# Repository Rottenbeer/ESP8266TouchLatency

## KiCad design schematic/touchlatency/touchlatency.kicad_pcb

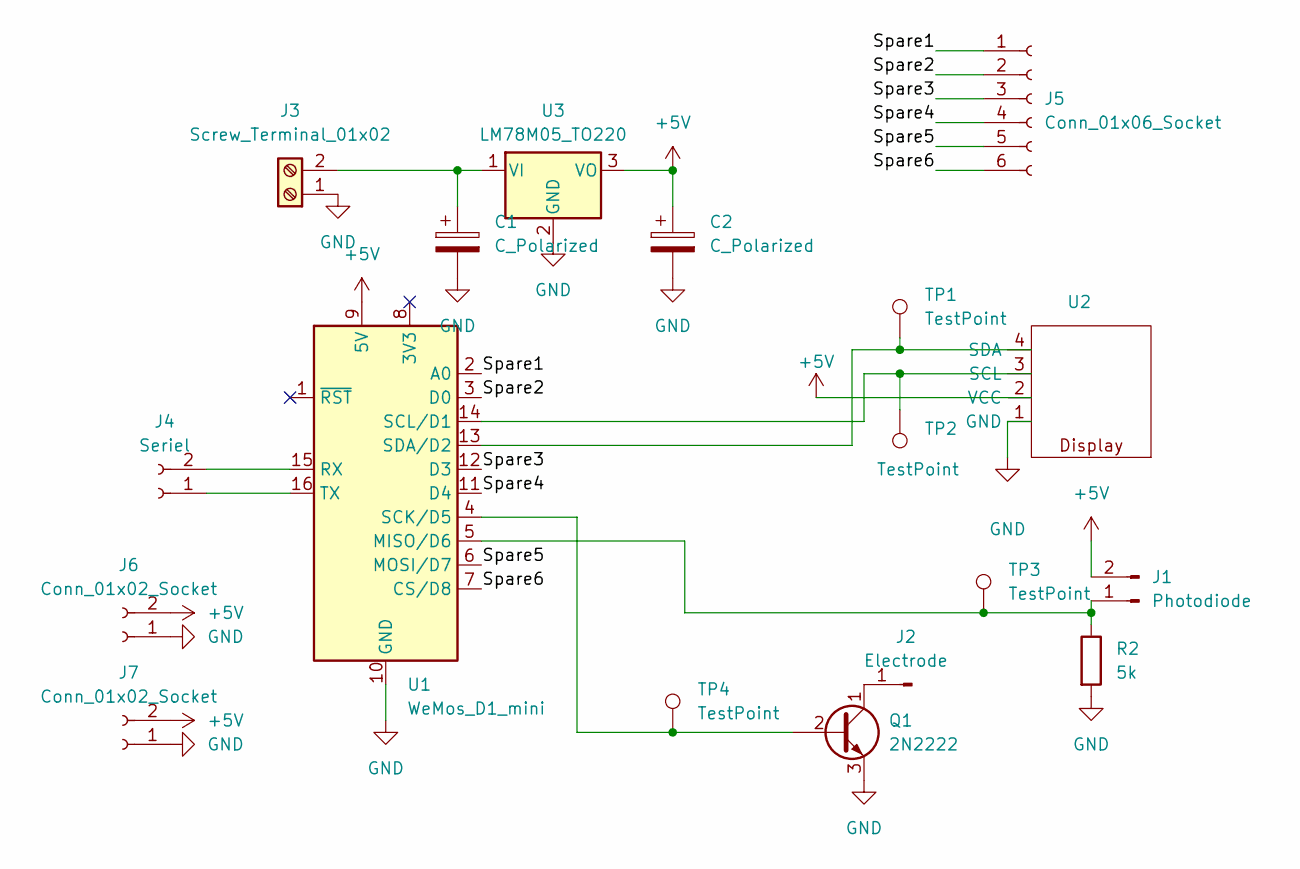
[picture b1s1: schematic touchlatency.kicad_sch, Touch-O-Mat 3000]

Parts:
C1, C2: C_Polarized; CP_Radial_D6.3mm_P2.50mm
J1: Photodiode; PinHeader_1x02_P2.54mm_Vertical
J2: Electrode; PinHeader_1x01_P2.54mm_Vertical
J3: Screw_Terminal_01x02; TerminalBlock_Altech_AK300-2_P5.00mm
J4: Seriel; PinHeader_1x02_P2.54mm_Vertical
J5: Conn_01x06_Socket; PinHeader_1x06_P2.54mm_Vertical
J6, J7: Conn_01x02_Socket; PinHeader_1x02_P2.54mm_Vertical
Q1: 2N2222; TO-92
R2: 5k; R_Axial_DIN0207_L6.3mm_D2.5mm_P10.16mm_Horizontal
TP1, TP2, TP3, TP4: TestPoint; TestPoint_Pad_D2.0mm
U1: WeMos_D1_mini; WEMOS_D1_mini_light
U2: display
U3: LM78M05_TO220; TO-220-3_Vertical

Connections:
+5V: C2.1, J1.2, J6.2, J7.2, U1.9 (5V), U2.2 (VCC), U3.3 (VO)
/Spare1: J5.1, U1.2 (A0)
/Spare2: J5.2, U1.3 (D0)
/Spare3: J5.3, U1.12 (D3)
/Spare4: J5.4, U1.11 (D4)
/Spare5: J5.5, U1.6 (MOSI/D7)
/Spare6: J5.6, U1.7 (CS/D8)
GND: C1.2, C2.2, J3.1, J6.1, J7.1, Q1.3 (E), R2.2, U1.10 (GND), U2.1 (GND), U3.2 (GND)
unnamed: J1.1, R2.1, TP3.1, U1.5 (MISO/D6)
unnamed: J2.1, Q1.1 (C)
unnamed: C1.1, J3.2, U3.1 (VI)
unnamed: J4.1, U1.16 (TX)
unnamed: J4.2, U1.15 (RX)
unnamed: Q1.2 (B), TP4.1, U1.4 (SCK/D5)
unnamed: TP2.1, U1.14 (SCL/D1), U2.3 (SCL)
unnamed: TP1.1, U1.13 (SDA/D2), U2.4 (SDA)

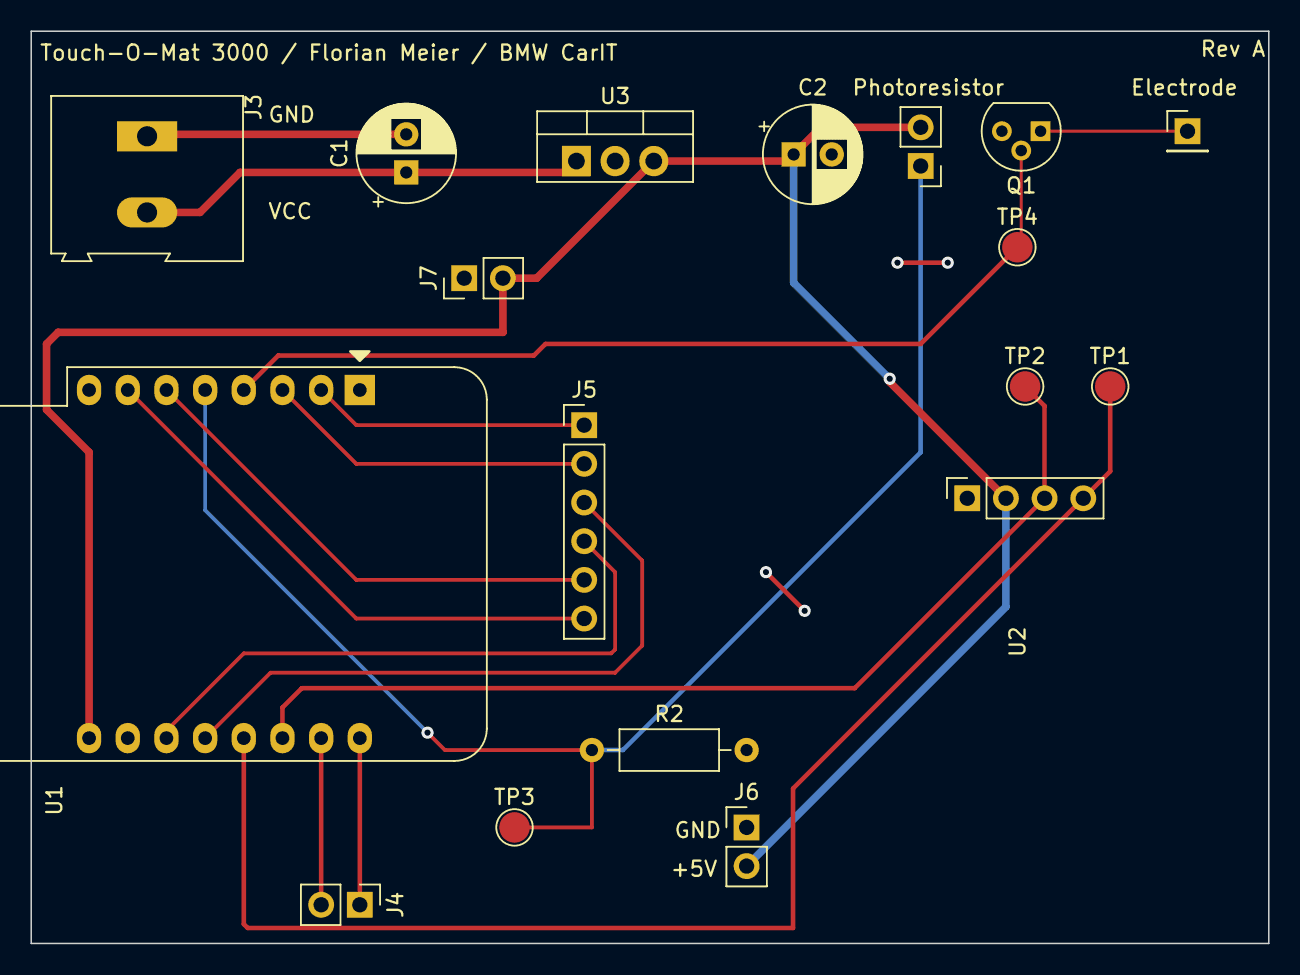
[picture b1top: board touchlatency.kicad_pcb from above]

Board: 2 copper layers, 81.3 x 59.9 mm, 18 parts (0 on the bottom side), 16 nets.

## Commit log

2023-12-03 init
2025-02-01 Updated platformio.ini
2025-02-01 vscode configs
2025-02-01 Adds .gitignore
2025-02-01 Adds kicad 8 schematic
2025-02-01 Tested and verified release with Rev A board
2025-02-07 Verified Phototransistor
2025-02-07 Rev B Phototransistor Update
